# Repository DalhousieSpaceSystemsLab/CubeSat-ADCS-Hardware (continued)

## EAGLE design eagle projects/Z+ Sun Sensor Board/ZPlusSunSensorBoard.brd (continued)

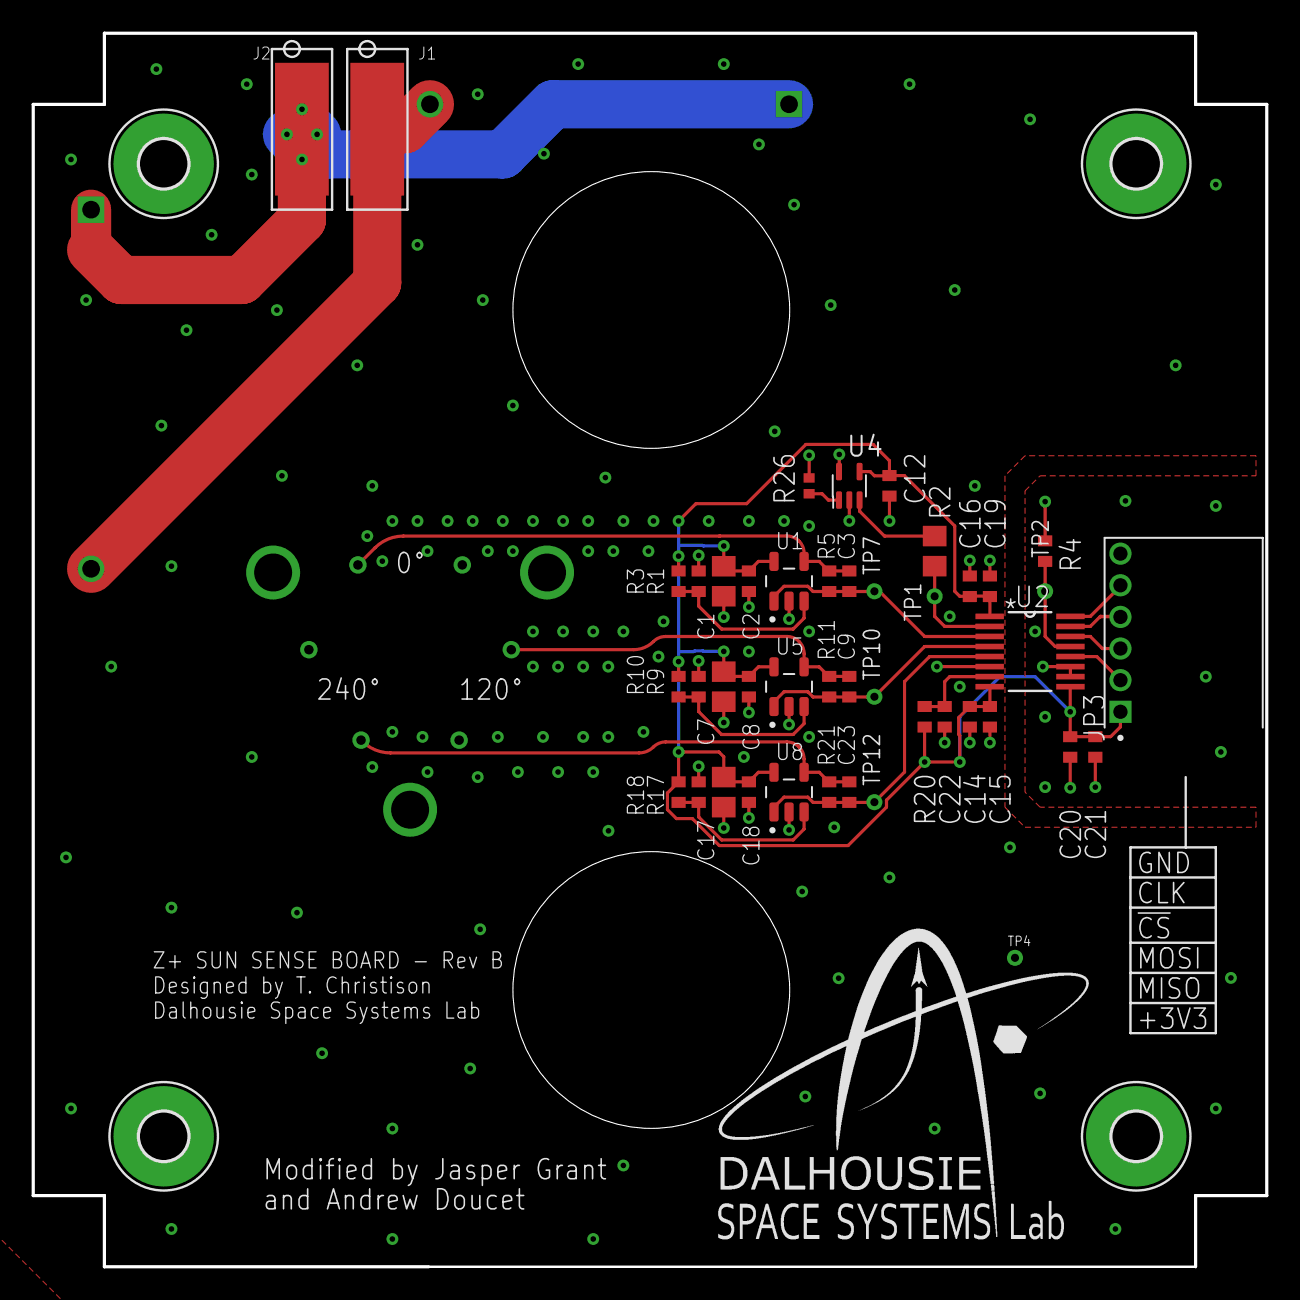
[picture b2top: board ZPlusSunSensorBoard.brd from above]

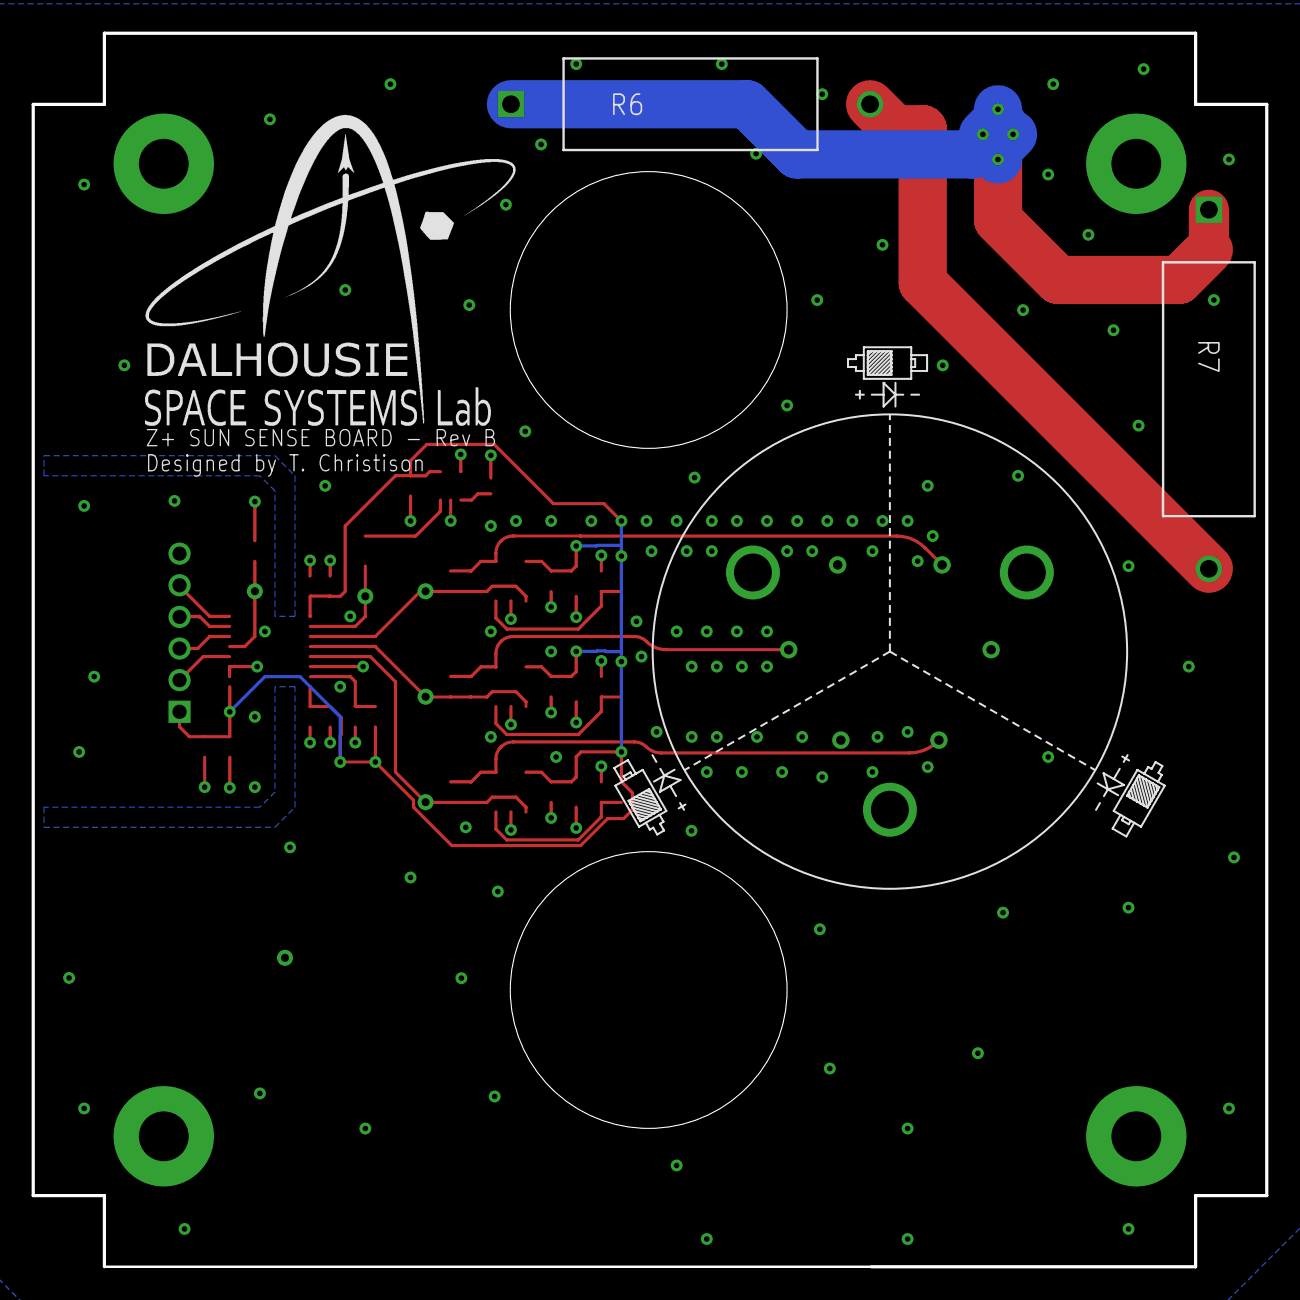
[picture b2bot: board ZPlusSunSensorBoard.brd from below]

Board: 2 copper layers, 78.0 x 78.0 mm, 54 parts (6 on the bottom side), 22 nets.

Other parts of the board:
J1: Power In; 2038638103
J2: Power Out; 2038638103
R6, R7: RS02B2R000FE70; ROX02B_VIS
U$2, U$3, U$4: PHOTODIODE_SILK

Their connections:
unnamed: J1.P$1, R6.2, R7.2
unnamed: J2.P$1, R6.1, R7.1

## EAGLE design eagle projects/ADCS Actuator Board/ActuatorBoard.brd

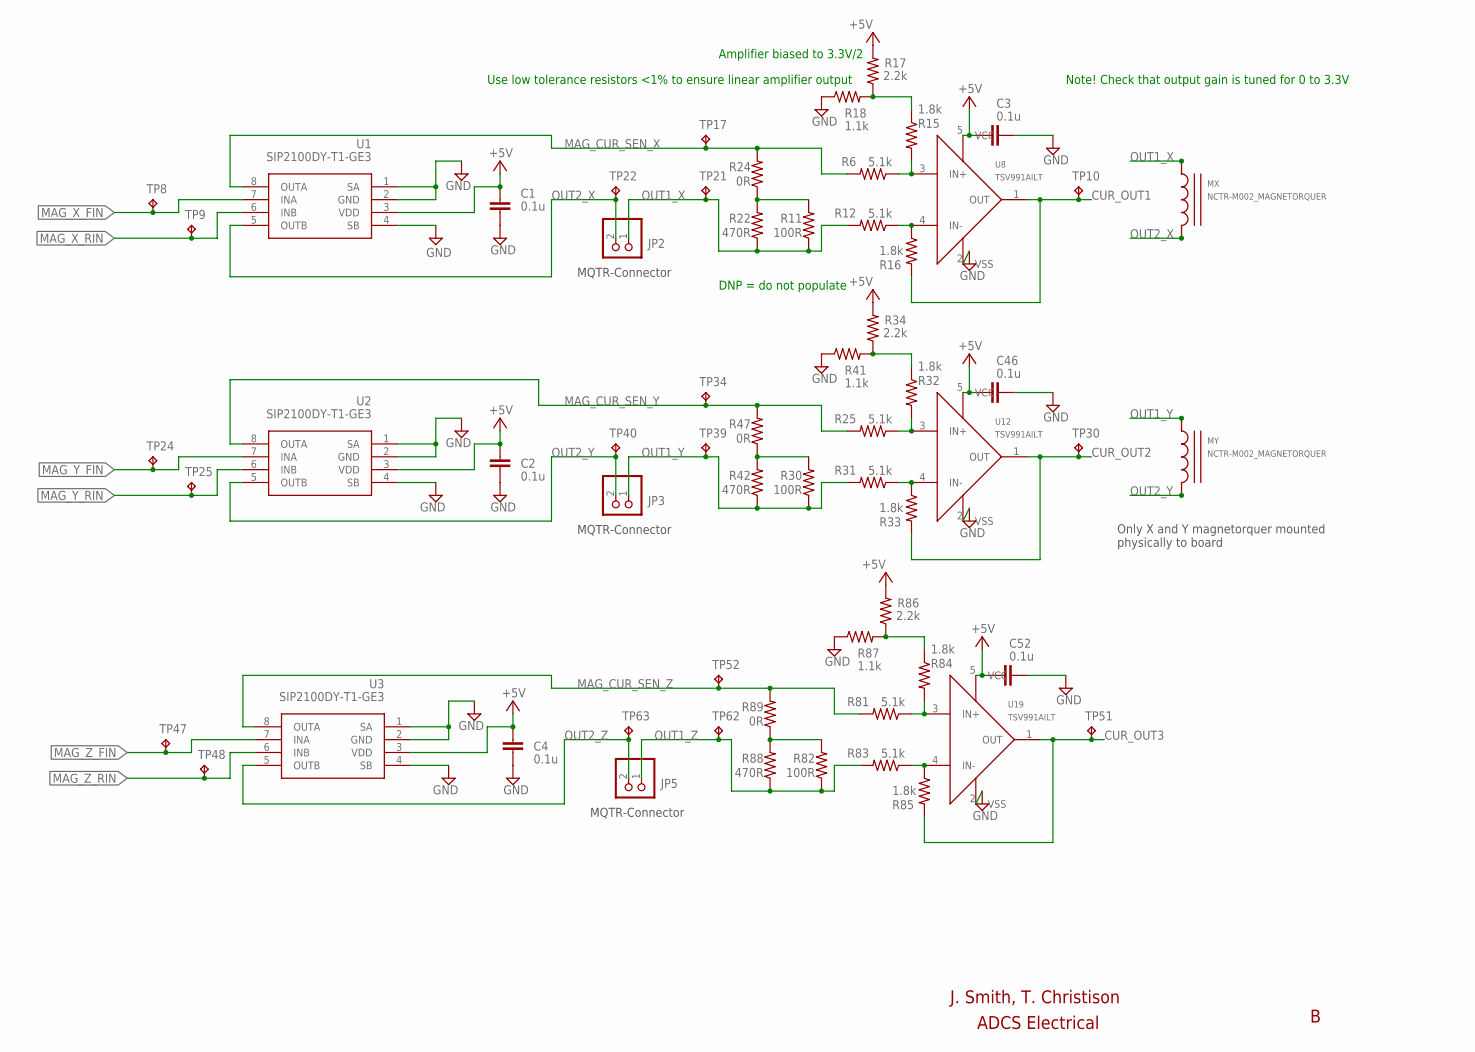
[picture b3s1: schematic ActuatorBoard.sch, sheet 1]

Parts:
C1, C2, C4: 0.1u; C0603
C3, C46, C52: 0.1u; C0402
JP2, JP3, JP5: PINHD-1X2; 1X02
MX: NCTR-M002_MAGNETORQUER; MAG_MOUNT_V3
MY: NCTR-M002_MAGNETORQUER; MAG_MOUNT_V3
R6, R12, R25, R31, R81, R83: 5.1k; R0402
R11, R30, R82: 100R; R0805
R15, R16, R32, R33, R84, R85: 1.8k; R0402
R17, R34, R86: 2.2k; R0402
R18, R41, R87: 1.1k; R0402
R22, R42, R88: 470R; R0805
R24, R47, R89: 0R; R0805
TP8, TP9, TP10, TP17, TP21, TP22, TP24, TP25, TP30, TP34, TP39, TP40, TP47, TP48, TP51, TP52, TP62, TP63: TESTPOINT; TP_P76H50
U1, U2, U3: SIP2100DY-T1-GE3; SOIC8P127_490X600X175L71X43N_SIP2100DY-T1-GE3
U8, U12, U19: TSV991AILT; SOT95P280X145-5N

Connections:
+5V: C1.1, C2.2, C3.1, C4.2, C46.1, C52.1, R17.2, R34.2, R86.2, U1.3 (VDD), U2.3 (VDD), U3.3 (VDD), U8.5 (VCC), U12.5 (VCC), U19.5 (VCC); also elsewhere on the board
CUR_OUT1: R16.2, TP10.1, U8.1 (OUT); also elsewhere on the board
CUR_OUT2: R33.2, TP30.1, U12.1 (OUT); also elsewhere on the board
CUR_OUT3: R85.2, TP51.1, U19.1 (OUT); also elsewhere on the board
GND: C1.2, C2.1, C3.2, C4.1, C46.2, C52.2, R18.1, R41.1, R87.1, U1.1 (SA), U1.2 (GND), U1.4 (SB), U2.1 (SA), U2.2 (GND), U2.4 (SB), U3.1 (SA), U3.2 (GND), U3.4 (SB), U8.2 (VSS), U12.2 (VSS), U19.2 (VSS); also elsewhere on the board
MAG_CUR_SEN_X: R6.2, R24.2, TP17.1, U1.8 (OUTA)
MAG_CUR_SEN_Y: R25.2, R47.2, TP34.1, U2.8 (OUTA)
MAG_CUR_SEN_Z: R81.2, R89.2, TP52.1, U3.8 (OUTA)
MAG_X_FIN: TP8.1, U1.7 (INA); also elsewhere on the board
MAG_X_RIN: TP9.1, U1.6 (INB); also elsewhere on the board
MAG_Y_FIN: TP24.1, U2.7 (INA); also elsewhere on the board
MAG_Y_RIN: TP25.1, U2.6 (INB); also elsewhere on the board
MAG_Z_FIN: TP47.1, U3.7 (INA); also elsewhere on the board
MAG_Z_RIN: TP48.1, U3.6 (INB); also elsewhere on the board
unnamed: R12.1, R16.1, U8.4 (IN-)
unnamed: R6.1, R15.2, U8.3 (IN+)
unnamed: R15.1, R17.1, R18.2
unnamed: R11.2, R22.2, R24.1
unnamed: R31.1, R33.1, U12.4 (IN-)
unnamed: R25.1, R32.2, U12.3 (IN+)
unnamed: R32.1, R34.1, R41.2
unnamed: R30.2, R42.2, R47.1
unnamed: R83.1, R85.1, U19.4 (IN-)
unnamed: R81.1, R84.2, U19.3 (IN+)
unnamed: R84.1, R86.1, R87.2
unnamed: R82.2, R88.2, R89.1
OUT1_X: JP2.1, R11.1, R12.2, R22.1, TP21.1
OUT1_Y: JP3.1, R30.1, R31.2, R42.1, TP39.1
OUT1_Z: JP5.1, R82.1, R83.2, R88.1, TP62.1
OUT2_X: JP2.2, TP22.1, U1.5 (OUTB)
OUT2_Y: JP3.2, TP40.1, U2.5 (OUTB)
OUT2_Z: JP5.2, TP63.1, U3.5 (OUTB)

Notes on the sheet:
Only X and Y magnetorquer mounted physically to board
J. Smith, T. Christison
MQTR-Connector
Note! Check that output gain is tuned for 0 to 3.3V
Amplifier biased to 3.3V/2
Use low tolerance resistors <1% to ensure linear amplifier output
DNP = do not populate
ADCS Electrical

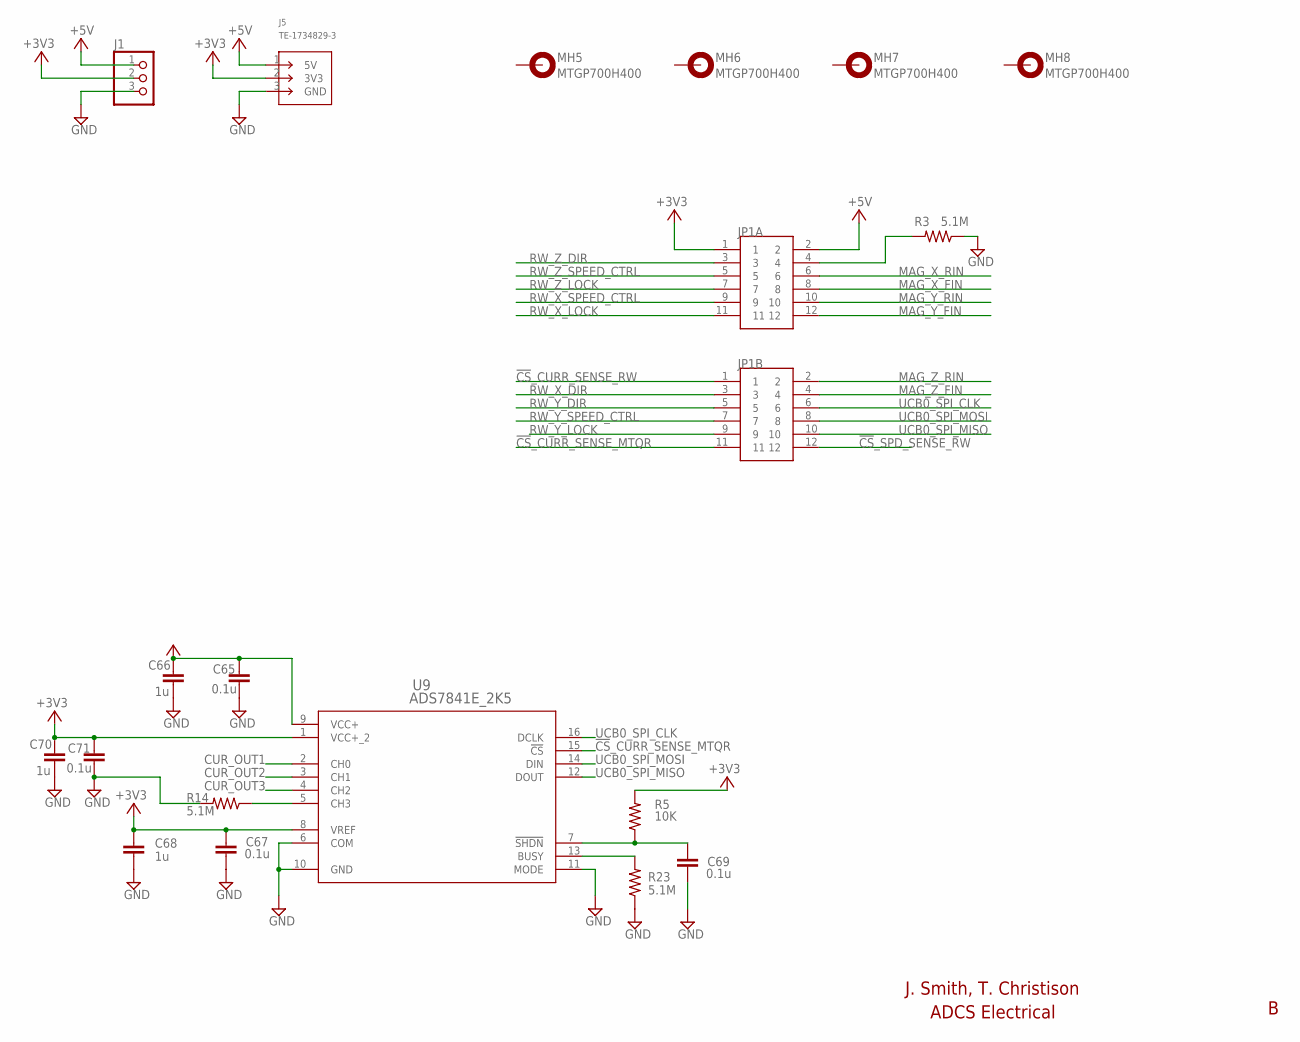
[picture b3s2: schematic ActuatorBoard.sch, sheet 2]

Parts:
C65, C67, C69, C71: 0.1u; C0402
C66, C68, C70: 1u; C0402
J1: PINHD-1X3; 1X03
J5: TE-1734829-3
JP1A, JP1B: 832-10-012-10-005000
MH5, MH6, MH7, MH8: MTGP700H400
R3, R14, R23: 5.1M; R0402
R5: 10K; R0402
U9: ADS7841E_2K5; DBQ16

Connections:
!CS!_CURR_SENSE_MTQR: JP1B.11, U9.15 (!CS)
!CS!_CURR_SENSE_RW: JP1B.1; also elsewhere on the board
!CS!_SPD_SENSE_RW: JP1B.12; also elsewhere on the board
+3V3: C65.1, C66.1, C67.1, C68.1, C70.1, C71.1, J1.2, J5.2 (3V3), JP1A.1, R5.2, U9.1 (VCC+_2), U9.8 (VREF), U9.9 (VCC+); also elsewhere on the board
+5V: J1.1, J5.1 (5V), JP1A.2; also elsewhere on the board
CUR_OUT1: U9.2 (CH0); also elsewhere on the board
CUR_OUT2: U9.3 (CH1); also elsewhere on the board
CUR_OUT3: U9.4 (CH2); also elsewhere on the board
GND: C65.2, C66.2, C67.2, C68.2, C69.2, C70.2, C71.2, J1.3, J5.3 (GND), R3.1, R14.2, R23.1, U9.6 (COM), U9.10 (GND), U9.11 (MODE); also elsewhere on the board
MAG_X_FIN: JP1A.8; also elsewhere on the board
MAG_X_RIN: JP1A.6; also elsewhere on the board
MAG_Y_FIN: JP1A.12; also elsewhere on the board
MAG_Y_RIN: JP1A.10; also elsewhere on the board
MAG_Z_FIN: JP1B.4; also elsewhere on the board
MAG_Z_RIN: JP1B.2; also elsewhere on the board
unnamed: JP1A.4, R3.2
unnamed: C69.1, R5.1, U9.7 (!SHDN)
unnamed: R23.2, U9.13 (BUSY)
unnamed: R14.1, U9.5 (CH3)
RW_X_DIR: JP1B.3; also elsewhere on the board
RW_X_LOCK: JP1A.11; also elsewhere on the board
RW_X_SPEED_CTRL: JP1A.9; also elsewhere on the board
RW_Y_DIR: JP1B.5; also elsewhere on the board
RW_Y_LOCK: JP1B.9; also elsewhere on the board
RW_Y_SPEED_CTRL: JP1B.7; also elsewhere on the board
RW_Z_DIR: JP1A.3; also elsewhere on the board
RW_Z_LOCK: JP1A.7; also elsewhere on the board
RW_Z_SPEED_CTRL: JP1A.5; also elsewhere on the board
UCB0_SPI_CLK: JP1B.6, U9.16 (DCLK); also elsewhere on the board
UCB0_SPI_MISO: JP1B.10, U9.12 (DOUT); also elsewhere on the board
UCB0_SPI_MOSI: JP1B.8, U9.14 (DIN); also elsewhere on the board

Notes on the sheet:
J. Smith, T. Christison
ADCS Electrical

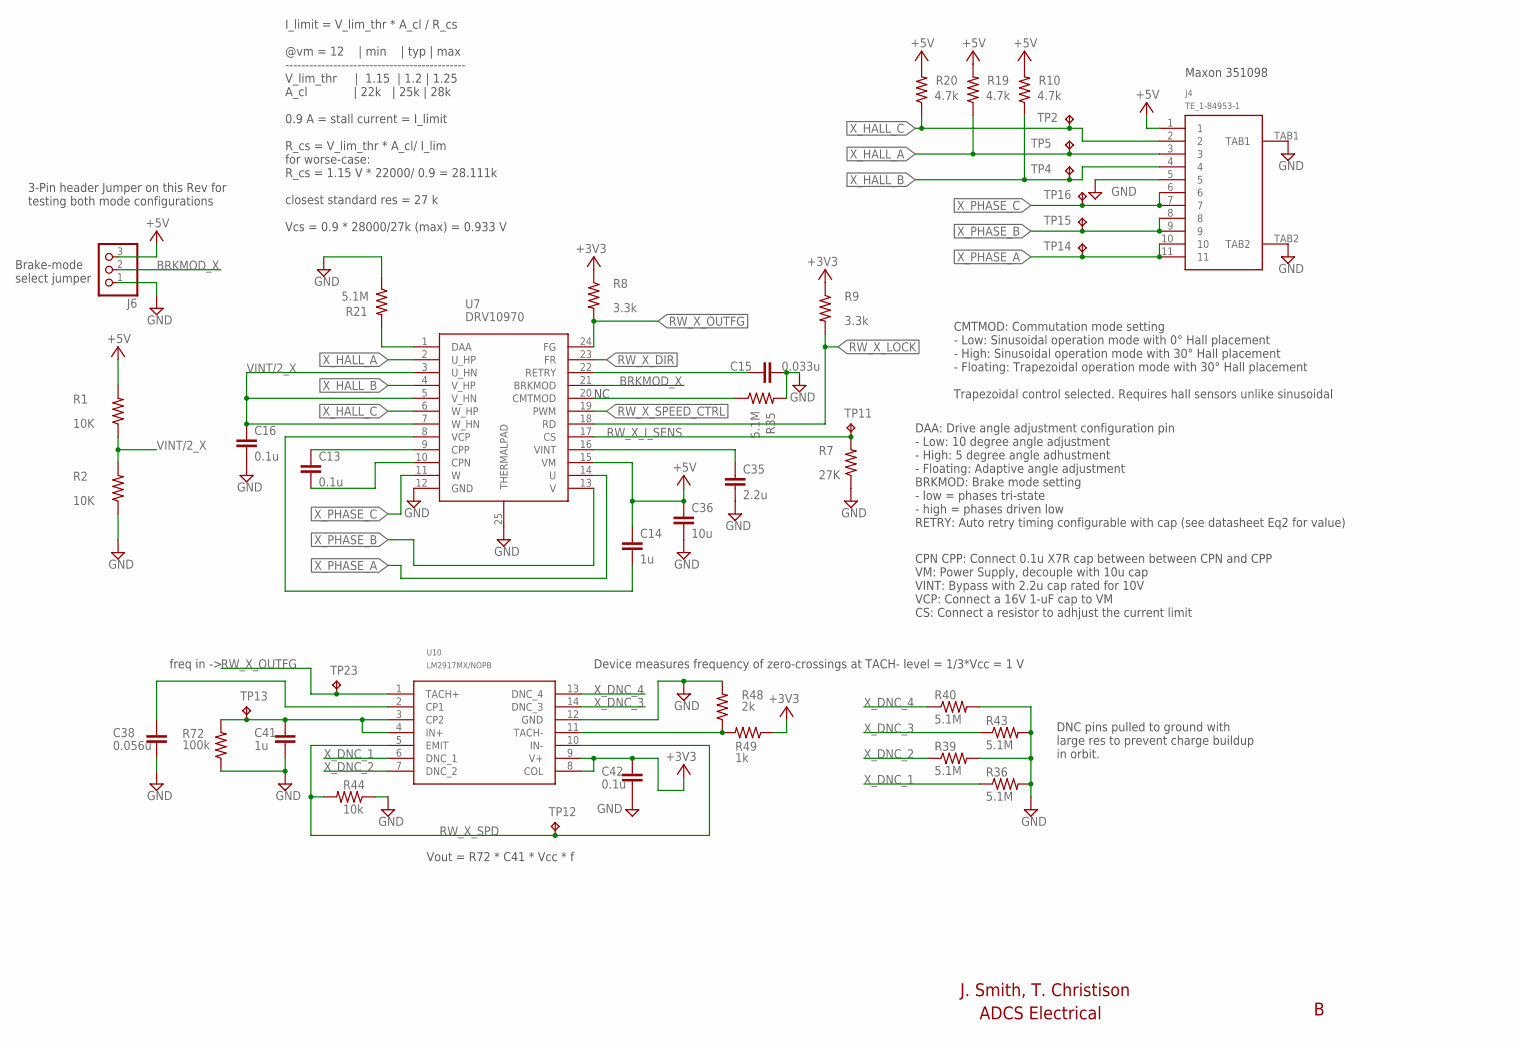
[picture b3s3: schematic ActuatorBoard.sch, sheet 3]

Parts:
C13, C16, C42: 0.1u; C0603
C14, C41: 1u; C0603
C15: 0.033u; C0603
C35: 2.2u; C0603
C36: 10u; C0603
C38: 0.056u; C0603
J4: TE_1-84953-1
J6: PINHD-1X3; 1X03
R1, R2: 10K; R0603
R7: 27K; R0603
R8, R9: 3.3k; R0603
R10, R19, R20: 4.7k; R0402
R21, R35, R36, R39, R40, R43: 5.1M; R0402
R44: 10k; R0603
R48: 2k; R0603
R49: 1k; R0603
R72: 100k; R0603
TP2, TP4, TP5, TP11, TP12, TP13, TP14, TP15, TP16, TP23: TESTPOINT; TP_P76H50
U7: DRV10970_MOTOR_DRIVERDRV10970; SOP65P640X120-25T240X328N
U10: LM2917MX/NOPB; SOIC14P127_865X600X175L83X41N_LM2917MX-NOPB

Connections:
+3V3: C42.2, R8.1, R9.1, R49.1, U10.8 (COL), U10.9 (V+); also elsewhere on the board
+5V: C14.1, C36.1, J4.1, J6.3, R1.2, R10.2, R19.2, R20.2, U7.15 (VM); also elsewhere on the board
BRKMOD_X: J6.2, U7.21 (BRKMOD)
GND: C15.2, C16.2, C35.2, C36.2, C38.1, C41.1, C42.1, J4.5, J4.TAB1, J4.TAB2, J6.1, R2.1, R7.1, R21.1, R35.2, R36.2, R39.2, R40.2, R43.2, R44.1, R48.2, R72.1, U7.12 (GND), U7.25 (THERMALPAD), U10.12 (GND); also elsewhere on the board
unnamed: C13.1, U7.9 (CPP)
unnamed: C14.2, U7.8 (VCP)
unnamed: C13.2, U7.10 (CPN)
unnamed: C35.1, U7.16 (VINT)
unnamed: C15.1, U7.22 (RETRY)
unnamed: R21.2, U7.1 (DAA)
unnamed: R35.1, U7.20 (CMTMOD)
unnamed: C41.2, R72.2, TP13.1, U10.3 (CP2), U10.4 (IN+)
unnamed: R48.1, R49.2, U10.11 (TACH-)
unnamed: C38.2, U10.2 (CP1)
RW_X_DIR: U7.23 (FR); also elsewhere on the board
RW_X_I_SENS: R7.2, TP11.1, U7.17 (CS); also elsewhere on the board
RW_X_LOCK: R9.2, U7.18 (RD); also elsewhere on the board
RW_X_OUTFG: R8.2, TP23.1, U7.24 (FG), U10.1 (TACH+)
RW_X_SPD: R44.2, TP12.1, U10.5 (EMIT), U10.10 (IN-); also elsewhere on the board
RW_X_SPEED_CTRL: U7.19 (PWM); also elsewhere on the board
VINT/2_X: C16.1, R1.1, R2.2, U7.3 (U_HN), U7.5 (V_HN), U7.7 (W_HN)
X_DNC_1: R36.1, U10.6 (DNC_1)
X_DNC_2: R39.1, U10.7 (DNC_2)
X_DNC_3: R43.1, U10.14 (DNC_3)
X_DNC_4: R40.1, U10.13 (DNC_4)
X_HALL_A: J4.3, R19.1, TP5.1, U7.2 (U_HP)
X_HALL_B: J4.4, R10.1, TP4.1, U7.4 (V_HP)
X_HALL_C: J4.2, R20.1, TP2.1, U7.6 (W_HP)
X_PHASE_A: J4.10, J4.11, TP14.1, U7.14 (U)
X_PHASE_B: J4.8, J4.9, TP15.1, U7.13 (V)
X_PHASE_C: J4.6, J4.7, TP16.1, U7.11 (W)

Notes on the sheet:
J. Smith, T. Christison
Device measures frequency of zero-crossings at TACH- level = 1/3*Vcc = 1 V
Vout = R72 * C41 * Vcc * f
freq in ->
DNC pins pulled to ground with large res to prevent charge buildup in orbit.
Brake-mode select jumper
CPN CPP: Connect 0.1u X7R cap between between CPN and CPP VM: Power Supply, decouple with 10u cap VINT: Bypass with 2.2u cap rated for 10V VCP: Connect a 16V 1-uF cap to VM CS: Connect a resistor to adhjust the current limit
DAA: Drive angle adjustment configuration pin - Low: 10 degree angle adjustment - High: 5 degree angle adhustment - Floating: Adaptive angle adjustment BRKMOD: Brake mode setting - low = phases tri-state - high = phases driven low RETRY: Auto retry timing configurable with cap (see datasheet Eq2 fo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
CMTMOD: Commutation mode setting - Low: Sinusoidal operation mode with 0° Hall placement - High: Sinusoidal operation mode with 30° Hall placement - Floating: Trapezoidal operation mode with 30° Hall placement Trapezoidal control selected. Requires hall sensors unlike sinusoidal
3-Pin header Jumper on this Rev for testing both mode configurations
I_limit = V_lim_thr * A_cl / R_cs @vm = 12 | min | typ | max --------------------------------------------- V_lim_thr | 1.15 | 1.2 | 1.25 A_cl | 22k | 25k | 28k 0.9 A = stall current = I_limit R_cs = V_lim_thr * A_cl/ I_lim for worse-case: R_cs = 1.15 V * 22000/ 0.9 = 28.111k closest standard res = 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
Maxon 351098
ADCS Electrical

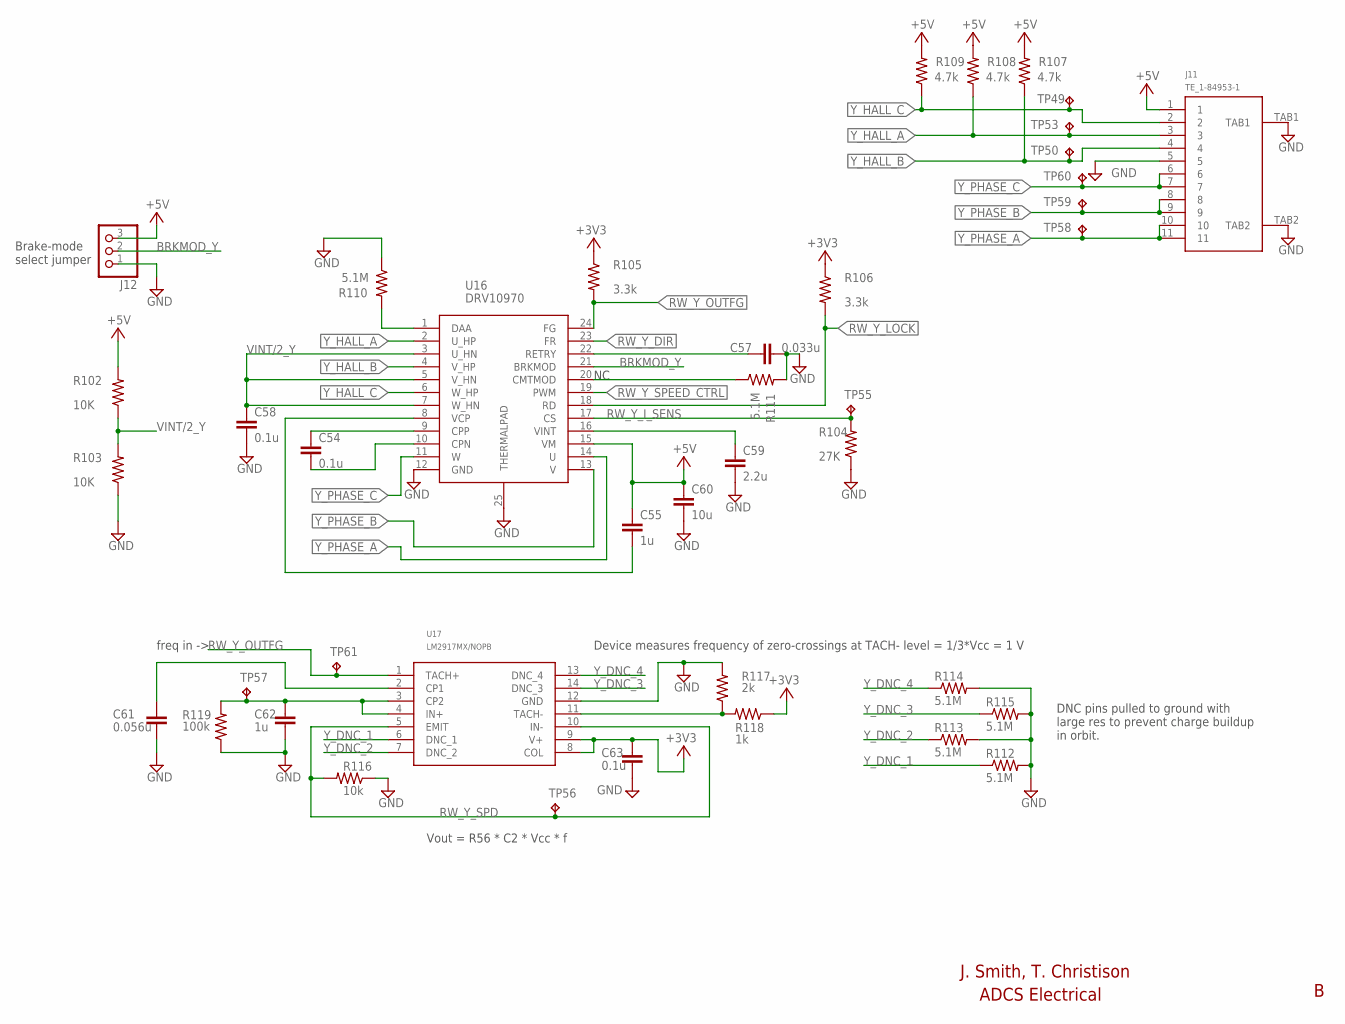
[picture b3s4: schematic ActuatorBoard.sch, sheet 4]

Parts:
C54, C58, C63: 0.1u; C0603
C55, C62: 1u; C0603
C57: 0.033u; C0603
C59: 2.2u; C0603
C60: 10u; C0603
C61: 0.056u; C0603
J11: TE_1-84953-1
J12: PINHD-1X3; 1X03
R102, R103: 10K; R0603
R104: 27K; R0603
R105, R106: 3.3k; R0603
R107, R108, R109: 4.7k; R0402
R110, R111, R112, R113, R114, R115: 5.1M; R0402
R116: 10k; R0603
R117: 2k; R0603
R118: 1k; R0603
R119: 100k; R0603
TP49, TP50, TP53, TP55, TP56, TP57, TP58, TP59, TP60, TP61: TESTPOINT; TP_P76H50
U16: DRV10970_MOTOR_DRIVERDRV10970; SOP65P640X120-25T240X328N
U17: LM2917MX/NOPB; SOIC14P127_865X600X175L83X41N_LM2917MX-NOPB

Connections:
+3V3: C63.2, R105.1, R106.1, R118.1, U17.8 (COL), U17.9 (V+); also elsewhere on the board
+5V: C55.1, C60.1, J11.1, J12.3, R102.2, R107.2, R108.2, R109.2, U16.15 (VM); also elsewhere on the board
BRKMOD_Y: J12.2, U16.21 (BRKMOD)
GND: C57.2, C58.2, C59.2, C60.2, C61.1, C62.1, C63.1, J11.5, J11.TAB1, J11.TAB2, J12.1, R103.1, R104.1, R110.1, R111.2, R112.2, R113.2, R114.2, R115.2, R116.1, R117.2, R119.1, U16.12 (GND), U16.25 (THERMALPAD), U17.12 (GND); also elsewhere on the board
unnamed: C54.1, U16.9 (CPP)
unnamed: C55.2, U16.8 (VCP)
unnamed: C54.2, U16.10 (CPN)
unnamed: C59.1, U16.16 (VINT)
unnamed: C57.1, U16.22 (RETRY)
unnamed: R110.2, U16.1 (DAA)
unnamed: R111.1, U16.20 (CMTMOD)
unnamed: C62.2, R119.2, TP57.1, U17.3 (CP2), U17.4 (IN+)
unnamed: R117.1, R118.2, U17.11 (TACH-)
unnamed: C61.2, U17.2 (CP1)
RW_Y_DIR: U16.23 (FR); also elsewhere on the board
RW_Y_I_SENS: R104.2, TP55.1, U16.17 (CS); also elsewhere on the board
RW_Y_LOCK: R106.2, U16.18 (RD); also elsewhere on the board
RW_Y_OUTFG: R105.2, TP61.1, U16.24 (FG), U17.1 (TACH+)
RW_Y_SPD: R116.2, TP56.1, U17.5 (EMIT), U17.10 (IN-); also elsewhere on the board
RW_Y_SPEED_CTRL: U16.19 (PWM); also elsewhere on the board
VINT/2_Y: C58.1, R102.1, R103.2, U16.3 (U_HN), U16.5 (V_HN), U16.7 (W_HN)
Y_DNC_1: R112.1, U17.6 (DNC_1)
Y_DNC_2: R113.1, U17.7 (DNC_2)
Y_DNC_3: R115.1, U17.14 (DNC_3)
Y_DNC_4: R114.1, U17.13 (DNC_4)
Y_HALL_A: J11.3, R108.1, TP53.1, U16.2 (U_HP)
Y_HALL_B: J11.4, R107.1, TP50.1, U16.4 (V_HP)
Y_HALL_C: J11.2, R109.1, TP49.1, U16.6 (W_HP)
Y_PHASE_A: J11.10, J11.11, TP58.1, U16.14 (U)
Y_PHASE_B: J11.8, J11.9, TP59.1, U16.13 (V)
Y_PHASE_C: J11.6, J11.7, TP60.1, U16.11 (W)

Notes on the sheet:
J. Smith, T. Christison
Device measures frequency of zero-crossings at TACH- level = 1/3*Vcc = 1 V
Vout = R56 * C2 * Vcc * f
freq in ->
DNC pins pulled to ground with large res to prevent charge buildup in orbit.
Brake-mode select jumper
ADCS Electrical

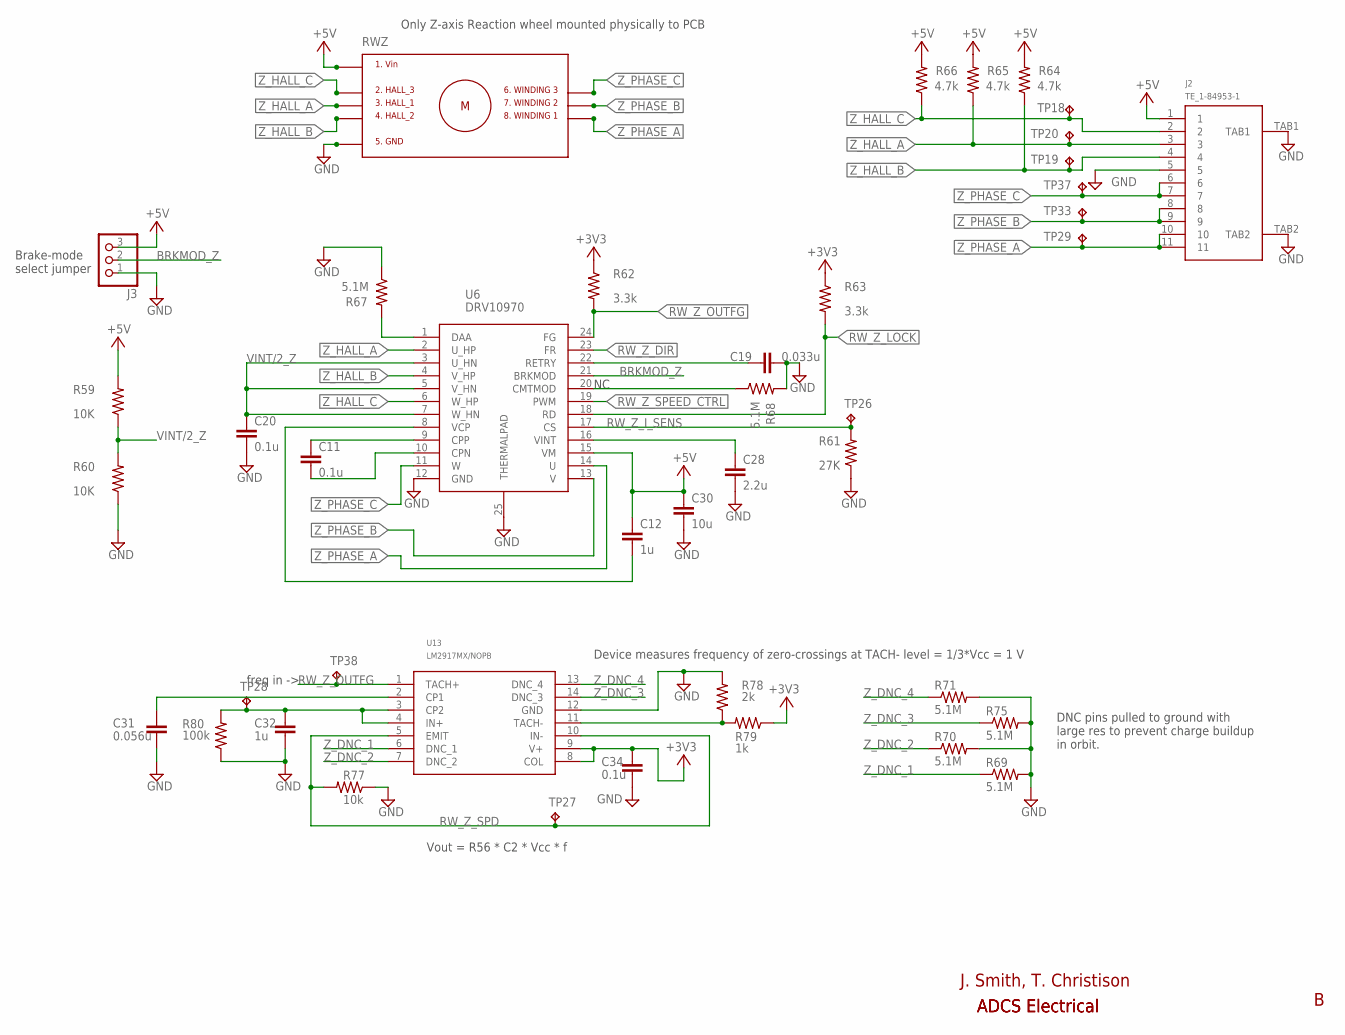
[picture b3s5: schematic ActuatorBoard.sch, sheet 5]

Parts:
C11, C20, C34: 0.1u; C0603
C12, C32: 1u; C0603
C19: 0.033u; C0603
C28: 2.2u; C0603
C30: 10u; C0603
C31: 0.056u; C0603
J2: TE_1-84953-1
J3: PINHD-1X3; 1X03
R59, R60: 10K; R0603
R61: 27K; R0603
R62, R63: 3.3k; R0603
R64, R65, R66: 4.7k; R0402
R67, R68, R69, R70, R71, R75: 5.1M; R0402
R77: 10k; R0603
R78: 2k; R0603
R79: 1k; R0603
R80: 100k; R0603
RWZ: REACTION_WHEEL_NOPINS_MAXON; RWA_NOPINS
TP18, TP19, TP20, TP26, TP27, TP28, TP29, TP33, TP37, TP38: TESTPOINT; TP_P76H50
U6: DRV10970_MOTOR_DRIVERDRV10970; SOP65P640X120-25T240X328N
U13: LM2917MX/NOPB; SOIC14P127_865X600X175L83X41N_LM2917MX-NOPB

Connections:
+3V3: C34.2, R62.1, R63.1, R79.1, U13.8 (COL), U13.9 (V+); also elsewhere on the board
+5V: C12.1, C30.1, J2.1, J3.3, R59.2, R64.2, R65.2, R66.2, U6.15 (VM); also elsewhere on the board
BRKMOD_Z: J3.2, U6.21 (BRKMOD)
GND: C19.2, C20.2, C28.2, C30.2, C31.1, C32.1, C34.1, J2.5, J2.TAB1, J2.TAB2, J3.1, R60.1, R61.1, R67.1, R68.2, R69.2, R70.2, R71.2, R75.2, R77.1, R78.2, R80.1, U6.12 (GND), U6.25 (THERMALPAD), U13.12 (GND); also elsewhere on the board
unnamed: C11.1, U6.9 (CPP)
unnamed: C12.2, U6.8 (VCP)
unnamed: C11.2, U6.10 (CPN)
unnamed: C28.1, U6.16 (VINT)
unnamed: C19.1, U6.22 (RETRY)
unnamed: R67.2, U6.1 (DAA)
unnamed: R68.1, U6.20 (CMTMOD)
unnamed: C32.2, R80.2, TP28.1, U13.3 (CP2), U13.4 (IN+)
unnamed: R78.1, R79.2, U13.11 (TACH-)
unnamed: C31.2, U13.2 (CP1)
RW_Z_DIR: U6.23 (FR); also elsewhere on the board
RW_Z_I_SENS: R61.2, TP26.1, U6.17 (CS); also elsewhere on the board
RW_Z_LOCK: R63.2, U6.18 (RD); also elsewhere on the board
RW_Z_OUTFG: R62.2, TP38.1, U6.24 (FG), U13.1 (TACH+)
RW_Z_SPD: R77.2, TP27.1, U13.5 (EMIT), U13.10 (IN-); also elsewhere on the board
RW_Z_SPEED_CTRL: U6.19 (PWM); also elsewhere on the board
VINT/2_Z: C20.1, R59.1, R60.2, U6.3 (U_HN), U6.5 (V_HN), U6.7 (W_HN)
Z_DNC_1: R69.1, U13.6 (DNC_1)
Z_DNC_2: R70.1, U13.7 (DNC_2)
Z_DNC_3: R75.1, U13.14 (DNC_3)
Z_DNC_4: R71.1, U13.13 (DNC_4)
Z_HALL_A: J2.3, R65.1, TP20.1, U6.2 (U_HP)
Z_HALL_B: J2.4, R64.1, TP19.1, U6.4 (V_HP)
Z_HALL_C: J2.2, R66.1, TP18.1, U6.6 (W_HP)
Z_PHASE_A: J2.10, J2.11, TP29.1, U6.14 (U)
Z_PHASE_B: J2.8, J2.9, TP33.1, U6.13 (V)
Z_PHASE_C: J2.6, J2.7, TP37.1, U6.11 (W)

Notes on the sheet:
Only Z-axis Reaction wheel mounted physically to PCB
J. Smith, T. Christison
Device measures frequency of zero-crossings at TACH- level = 1/3*Vcc = 1 V
Vout = R56 * C2 * Vcc * f
freq in ->
DNC pins pulled to ground with large res to prevent charge buildup in orbit.
Brake-mode select jumper
ADCS Electrical

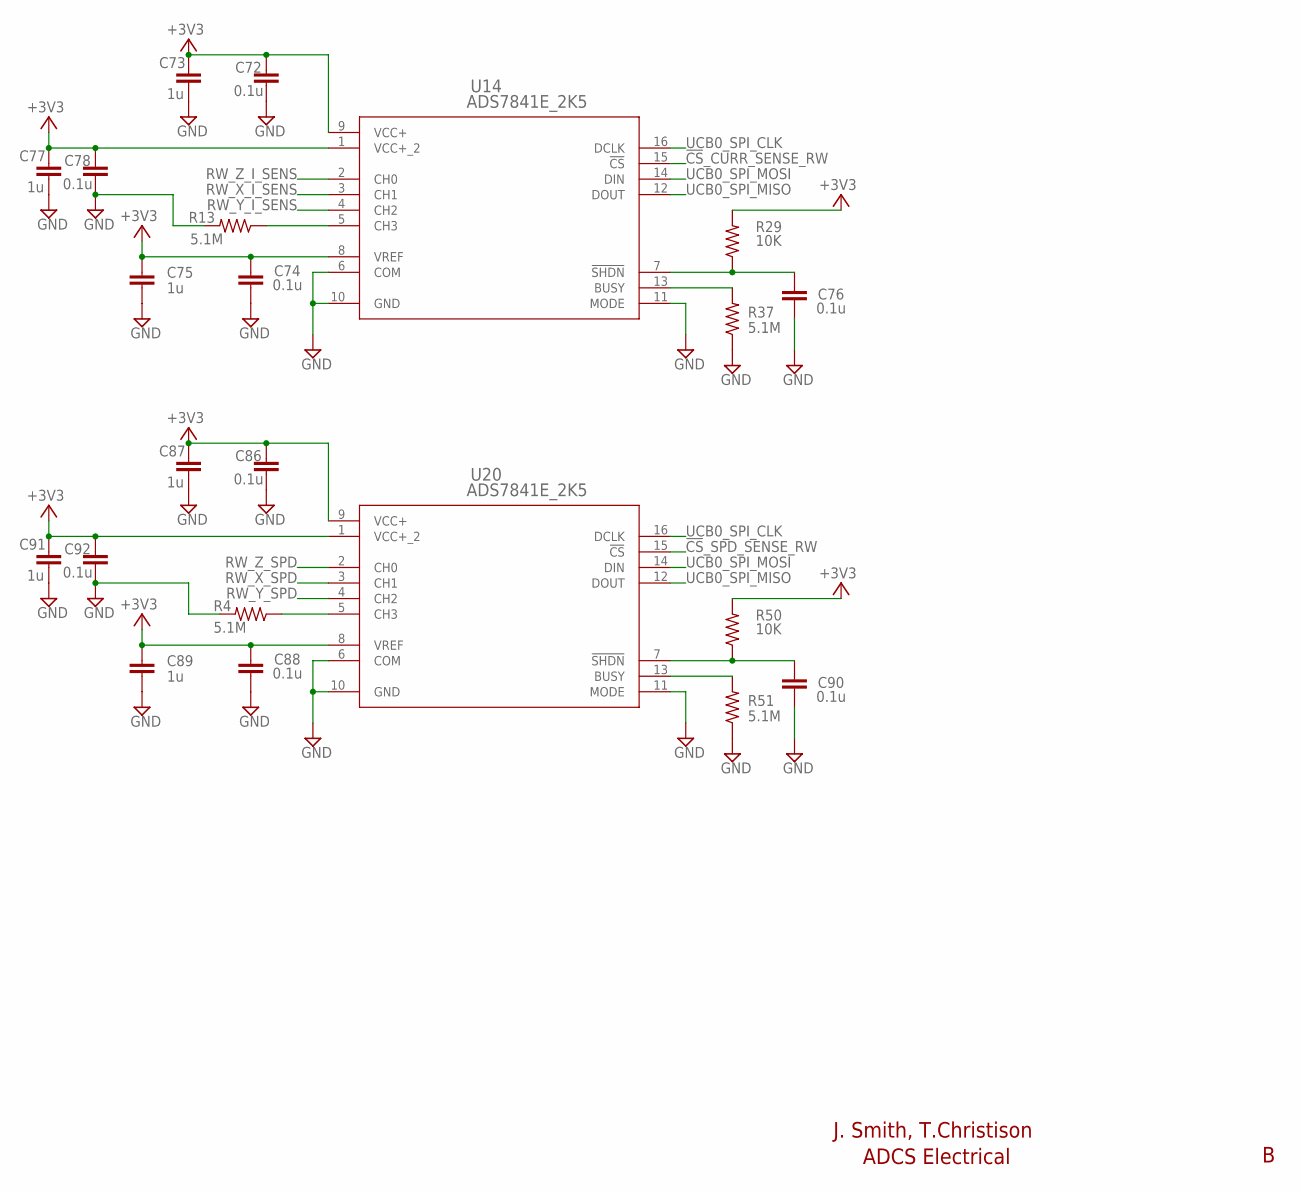
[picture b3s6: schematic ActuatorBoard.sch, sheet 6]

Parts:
C72, C74, C76, C78, C86, C88, C90, C92: 0.1u; C0402
C73, C75, C77, C87, C89, C91: 1u; C0402
R4, R13, R37, R51: 5.1M; R0402
R29, R50: 10K; R0402
U14, U20: ADS7841E_2K5; DBQ16

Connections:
!CS!_CURR_SENSE_RW: U14.15 (!CS); also elsewhere on the board
!CS!_SPD_SENSE_RW: U20.15 (!CS); also elsewhere on the board
+3V3: C72.1, C73.1, C74.1, C75.1, C77.1, C78.1, C86.1, C87.1, C88.1, C89.1, C91.1, C92.1, R29.2, R50.2, U14.1 (VCC+_2), U14.8 (VREF), U14.9 (VCC+), U20.1 (VCC+_2), U20.8 (VREF), U20.9 (VCC+); also elsewhere on the board
GND: C72.2, C73.2, C74.2, C75.2, C76.2, C77.2, C78.2, C86.2, C87.2, C88.2, C89.2, C90.2, C91.2, C92.2, R4.2, R13.2, R37.1, R51.1, U14.6 (COM), U14.10 (GND), U14.11 (MODE), U20.6 (COM), U20.10 (GND), U20.11 (MODE); also elsewhere on the board
unnamed: C76.1, R29.1, U14.7 (!SHDN)
unnamed: C90.1, R50.1, U20.7 (!SHDN)
unnamed: R37.2, U14.13 (BUSY)
unnamed: R13.1, U14.5 (CH3)
unnamed: R51.2, U20.13 (BUSY)
unnamed: R4.1, U20.5 (CH3)
RW_X_I_SENS: U14.3 (CH1); also elsewhere on the board
RW_X_SPD: U20.3 (CH1); also elsewhere on the board
RW_Y_I_SENS: U14.4 (CH2); also elsewhere on the board
RW_Y_SPD: U20.4 (CH2); also elsewhere on the board
RW_Z_I_SENS: U14.2 (CH0); also elsewhere on the board
RW_Z_SPD: U20.2 (CH0); also elsewhere on the board
UCB0_SPI_CLK: U14.16 (DCLK), U20.16 (DCLK); also elsewhere on the board
UCB0_SPI_MISO: U14.12 (DOUT), U20.12 (DOUT); also elsewhere on the board
UCB0_SPI_MOSI: U14.14 (DIN), U20.14 (DIN); also elsewhere on the board

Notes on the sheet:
J. Smith, T.Christison
ADCS Electrical
